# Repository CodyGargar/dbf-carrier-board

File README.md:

# MIT DBF Logger + Stabilizer board (Rev B)

Everything for the Teensy 4.1 board that stabilizes the plane, sends telemetry to the pilot's radio and logs every flight.
Status: **routed and order-ready (Rev B)**. Every connection is routed, the design check has no electrical errors, and the JLCPCB files are in [jlcpcb/](jlcpcb/). All pin orders are checked (see Open questions).

| File | What it is |
|---|---|
| [wiring/avionics-wiring.png](wiring/avionics-wiring.png) | **Full avionics wiring diagram**: both batteries, receiver, board, servos, ESC and motor (SVG next to it) |
| [design-spec.md](design-spec.md) | How the board works: failover, ESC telemetry, power, pins, bring-up order |
| [kicad/dbf-carrier.kicad_pro](kicad/dbf-carrier.kicad_pro) | KiCad project; open it in KiCad 7 or newer |
| [kicad/board-top.png](kicad/board-top.png) | Picture of the routed board (red = top copper, blue = bottom copper) |
| [kicad/board-inner-planes.png](kicad/board-inner-planes.png) | The two inner layers: ground plane and servo-power plane |
| [jlcpcb/ORDERING.md](jlcpcb/ORDERING.md) | How to order: Gerber zip, parts list (BOM) and placement file (CPL) for JLCPCB |
| [kicad/drc-report.txt](kicad/drc-report.txt) | Design check output: 0 shorts, 0 clearance errors, 0 unconnected pins |
| [pinout.csv](pinout.csv) | Which Teensy pin does what |
| [parts-list.xlsx](parts-list.xlsx) / [bom.csv](bom.csv) | Parts with links and prices; about $369 for one plane set + 2 built boards |
| [module-menu.md](module-menu.md) | Every module, and whether it is needed or optional |
| [rules-check-2027.md](rules-check-2027.md) | 2027 rules draft and last year's Q&A, checked against the board |

Online versions:
- Board slide deck: https://claude.ai/artifact/GLwo9eBtNZT7Tdii5Wy8GB

## Changes on 2026-11-07 (before ordering)

- **RX CRSF connector (J6) now matches the RadioMaster ER8's CRSF port** (⊖, +, RX, TX), so a standard pin-1-to-pin-1 JST-GH cable works. Pin 2 (the receiver's 5 V) is left unconnected on the board.
- **ESC is the Castle Phoenix Edge 100** (34 V, 100 A, 5 A BEC), not the Edge Lite. The **+ pin of the T column on TO SERVOS + ESC is now unconnected**, so the ESC's BEC can never feed the servo rail, even if its red wire is left in.
- Rerouted, design check rerun (0 unconnected pads, no new warnings), JLCPCB files regenerated. **Re-upload the Gerber zip, BOM and CPL to JLCPCB before paying, and set the part rotations again** (see [jlcpcb/ORDERING.md](jlcpcb/ORDERING.md)).

## Open questions

Nothing blocks the JLCPCB order now. Still open:

1. Confirm in this year's Q&A that a custom microcontroller stabilization system is allowed. Ask about the optional inline current sensor too (the ESC's own telemetry avoids it).
2. Bench-test Castle Link Live with the board's 10k pull-up to 3.3 V (Castle's adapters use 10k to the receiver's +). If it doesn't work, R9 can be changed by hand.
3. **Servo voltage:** the receiver pack is a 2S LiPo (8.4 V fully charged) and feeds the servos directly. **Every servo must be rated HV (8.4 V).** Also confirm the ER8 accepts 8.4 V on its servo pins. If any servo is 6 V only, switch to a 2S LiFe (7.2 V full) pack.
4. Confirm how the 2 drop servos are wired (Y-cable on receiver channel 8).

Done:
- **Batteries chosen (2026-11-07):** motor pack is a Turnigy nano-tech 6S LiPo, 22.2 V, 3300 mAh (73 Wh, under the 100 Wh limit; 25.2 V full, well under the ESC's 34 V). Receiver pack is a 2S LiPo, 7.4 V, 1300 mAh (9.6 Wh).
- **Pololu S7V7F5 pin order checked:** GND is the middle pin, with VIN and VOUT on the ends (two independent CAD libraries for this module agree; Pololu lists them as VIN, GND, VOUT). The board matches. The only way to get it wrong is to put the module in backwards, so the board now has **VIN / GND / OUT** printed under the pads: VIN goes in the square pad.
- **Buzzer + pad checked:** two footprints drawn from the CMT-8504 datasheet (one marks the pads P and N, one cites the datasheet's rev 09/11/2024 land pattern) both put **+ at the top-left pad and − at the bottom-left**, with the right pair as dummy pads. KiCad's pad 1 is the same top-left pad, and the board wires it to +. Correct as is.
- Receiver confirmed as a **RadioMaster ER8 2.4 GHz**. Its CRSF port order (⊖, +, RX, TX) was checked from a photo, and the board now matches it.

## ESC setup (Castle Phoenix Edge 100)

1. Pull the **red** wire out of the ESC's throttle plug (lift the tab with a needle) and shrink-wrap it. The board already ignores it, but this shows the BEC is disabled at tech inspection (rules 3.2.3).
2. With a Castle Link USB adapter, turn **Link Live on**, set **fixed throttle endpoints** (not auto-calibrate), and check the low-voltage cutoff matches your cell count.
3. Plug the throttle lead into **T** on TO SERVOS + ESC, with the signal wire on S.

## CRSF cable (ER8 to board)

Use a JST-GH 1.25 mm 4-pin cable wired **pin 1 to pin 1** (same direction), not a reversed one. Before plugging in the Teensy, power the receiver and check with a meter: 5 V should appear only on J6 pin 2.

## Regenerating the board

The board is generated by Python scripts that use KiCad's `pcbnew` module (KiCad 7). Run them in order from the `kicad/` folder:

```
python3 make_board.py     # places the parts
python3 route_board.py    # routes every connection
python3 finish_board.py   # planes, design check, JLCPCB files
```

The wiring diagram is drawn by `wiring/make_wiring.py`.

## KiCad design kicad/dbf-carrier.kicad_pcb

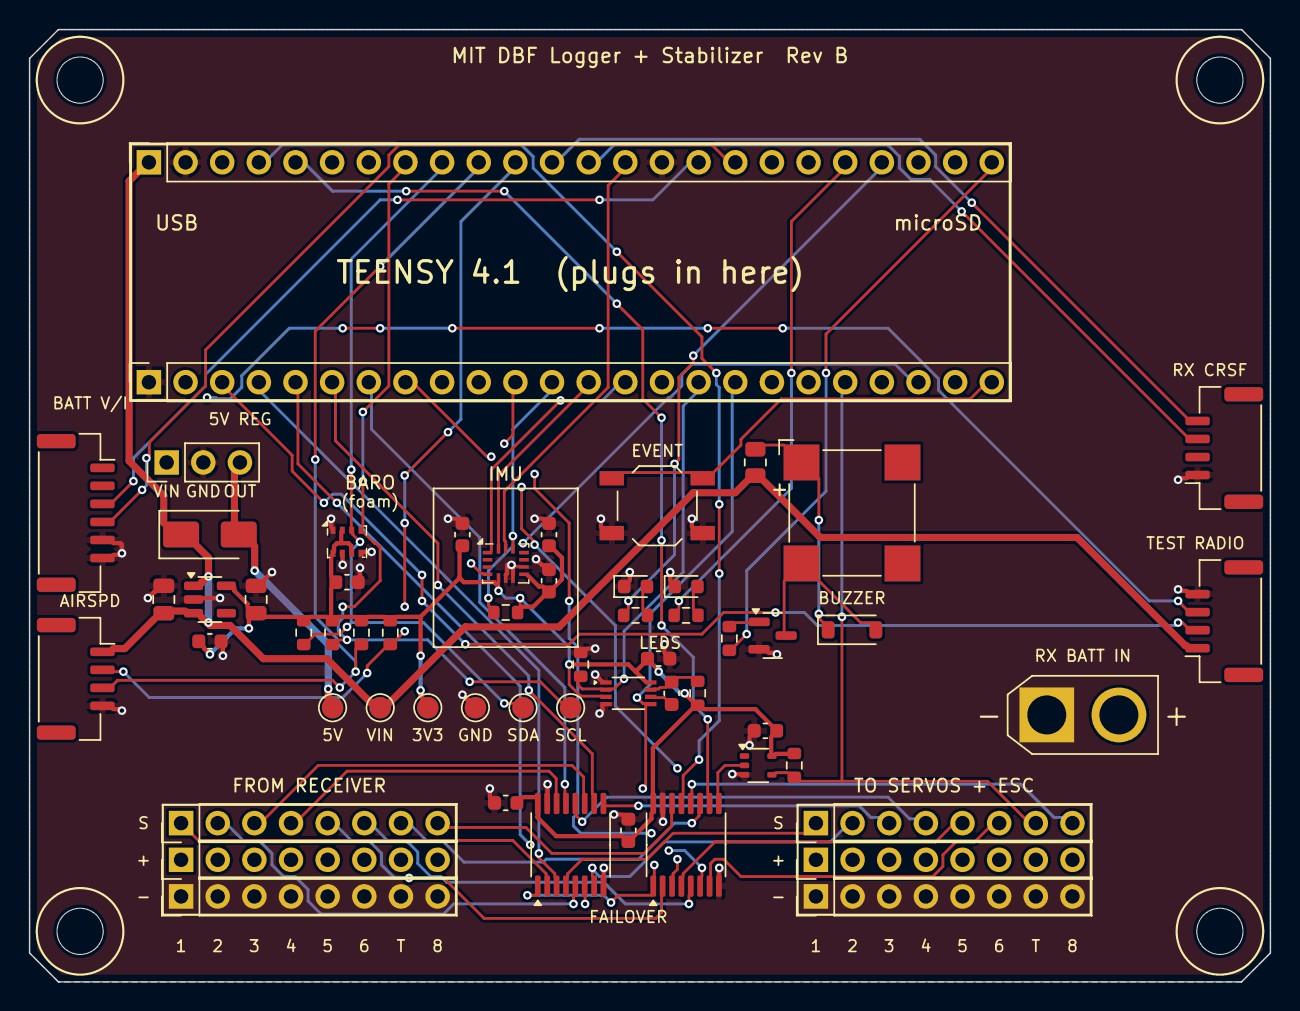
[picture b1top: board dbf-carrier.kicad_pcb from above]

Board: 4 copper layers, 86.0 x 66.0 mm, 62 parts (0 on the bottom side), 58 nets.

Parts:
BZ1: Buzzer; MagneticBuzzer_CUI_CMT-8504-100-SMT
C1, C2: 10uF; C_0805_2012Metric
C3, C4, C5, C6, C8, C9, C10, C11: 100nF; C_0603_1608Metric
C7: watchdog RC; C_0603_1608Metric
C12: 2.2uF; C_0603_1608Metric
D1: SS24 Schottky; D_SMA
D2: GRN; LED_0603_1608Metric
D3: RED; LED_0603_1608Metric
D4: 1N4148W flyback; D_SOD-123
H1, H2, H3, H4: M3; MountingHole_3.2mm_M3
J1: Teensy row A; PinSocket_1x24_P2.54mm_Vertical
J2: Teensy row B; PinSocket_1x24_P2.54mm_Vertical
J4: Airspeed; JST_GH_SM04B-GHS-TB_1x04-1MP_P1.25mm_Horizontal
J6: RX CRSF; JST_GH_SM04B-GHS-TB_1x04-1MP_P1.25mm_Horizontal
J7: Power module (sense only); JST_GH_SM06B-GHS-TB_1x06-1MP_P1.25mm_Horizontal
J11: Test radio (testing only); JST_GH_SM04B-GHS-TB_1x04-1MP_P1.25mm_Horizontal
J12: Rx battery in (from radio switch); AMASS_XT30U-M_1x02_P5.0mm_Vertical
J21: FROM RECEIVER S; PinHeader_1x08_P2.54mm_Vertical
J22: FROM RECEIVER +; PinHeader_1x08_P2.54mm_Vertical
J23: FROM RECEIVER -; PinHeader_1x08_P2.54mm_Vertical
J31: TO SERVOS + ESC S; PinHeader_1x08_P2.54mm_Vertical
J32: TO SERVOS + ESC +; PinHeader_1x08_P2.54mm_Vertical
J33: TO SERVOS + ESC -; PinHeader_1x08_P2.54mm_Vertical
Q1: MMBT3904 NPN; SOT-23
R1: 10k CS pull-up; R_0603_1608Metric
R2: 4.7k SDA; R_0603_1608Metric
R3: 4.7k SCL; R_0603_1608Metric
R4: 2.2k SDA1; R_0603_1608Metric
R5: 2.2k SCL1; R_0603_1608Metric
R6, R7: 1k; R_0603_1608Metric
R8: watchdog RC; R_0603_1608Metric
R9: 10k throttle pull-up; R_0603_1608Metric
R10: 1k buzzer base; R_0603_1608Metric
R11: 100k heartbeat pull-down; R_0603_1608Metric
R12: 18R buzzer current limit; R_0805_2012Metric
SW1: Event button; SW_SPST_TL3342
TP1: 5V; TestPoint_Pad_D1.5mm
TP2: VIN; TestPoint_Pad_D1.5mm
TP3: 3V3; TestPoint_Pad_D1.5mm
TP4: GND; TestPoint_Pad_D1.5mm
TP5: SDA; TestPoint_Pad_D1.5mm
TP6: SCL; TestPoint_Pad_D1.5mm
U2: ICM-42688-P; Bosch_LGA-14_3x2.5mm_P0.5mm
U3: DPS368; Bosch_LGA-8_2x2.5mm_P0.65mm_ClockwisePinNumbering
U4: AP2112K-3.3; SOT-23-5
U5: Pololu S7V7F5 5V reg; PinHeader_1x03_P2.54mm_Vertical
U6: SN74LVC157A ch1-4; TSSOP-16_4.4x5mm_P0.65mm
U7: SN74LVC157A ch5-8; TSSOP-16_4.4x5mm_P0.65mm
U8: 74LVC1G123 watchdog; VSSOP-8_2.3x2mm_P0.5mm
U9: 74LVC1G07 throttle open-drain; SOT-353_SC-70-5

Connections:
+3V3S: C2.1, C3.1, C4.1, C5.1, C6.1, C8.2, C9.1, C10.1, C11.2, C12.1, R1.2, R2.2, R3.2, R4.2, R5.2, R8.2, R9.2, TP3.1, U2.5, U2.8, U3.2, U3.6, U3.8, U4.5, U6.16, U7.16, U8.3, U8.8, U9.5
+5V: D1.2, TP1.1, U5.3
BATT_I: J1.16, J7.3
BATT_V: J1.17, J7.4
BTN: J2.24, SW1.1
BUZ: J1.24, R10.1
BUZ_B: Q1.1, R10.2
BUZ_C: BZ1.2, D4.2, Q1.3
BUZ_P: BZ1.1, D4.1, R12.2
CRSF_RX: J1.12, J6.4
CRSF_TX: J1.13, J6.3
GND: C1.2, C2.2, C3.2, C4.2, C5.2, C6.2, C8.1, C9.2, C10.2, C11.1, C12.2, D2.1, D3.1, J1.2, J1.15, J2.1, J4.4, J6.1, J7.5, J7.6, J11.4, J12.1, J23.1, J23.2, J23.3, J23.4, J23.5, J23.6, J23.7, J23.8, J33.1, J33.2, J33.3, J33.4, J33.5, J33.6, J33.7, J33.8, Q1.2, R11.2, SW1.2, TP4.1, U2.6, U2.7, U2.9, U3.1, U3.5, U3.7, U4.2, U5.2, U6.8, U6.15, U7.8, U7.15, U8.1, U8.4, U9.3
HEARTBEAT: J2.16, R11.1, U8.2
IMU_CS: J2.12, R1.1, U2.12
IMU_INT: J2.22, U2.4
IMU_MISO: J2.14, U2.1
IMU_MOSI: J2.13, U2.14
IMU_SCK: J1.14, U2.13
LED_G: J1.21, R6.1
LED_G_A: D2.2, R6.2
LED_R: J1.20, R7.1
LED_R_A: D3.2, R7.2
OUT_CH1: J31.1, U6.4
OUT_CH2: J31.2, U6.7
OUT_CH3: J31.3, U6.9
OUT_CH4: J31.4, U6.12
OUT_CH5: J31.5, U7.4
OUT_CH6: J31.6, U7.7
OUT_CH8: J31.8, U7.12
OUT_T: J2.20, J31.7, R9.1, U9.4
PWM_CH1: J2.4, U6.3
PWM_CH2: J2.5, U6.6
PWM_CH3: J2.6, U6.10
PWM_CH4: J2.7, U6.13
PWM_CH5: J2.8, U7.3
PWM_CH6: J2.11, U7.6
PWM_CH8: J1.4, U7.13
PWM_CHT: J1.5, U7.10
RX_CH1: J21.1, U6.2
RX_CH2: J21.2, U6.5
RX_CH3: J21.3, U6.11
RX_CH4: J21.4, U6.14
RX_CH5: J21.5, U7.2
RX_CH6: J21.6, U7.5
RX_CH8: J21.8, U7.14
RX_CHT: J21.7, U7.11
SCL: J1.8, R3.1, TP6.1, U3.4
SCL1: J1.11, J4.2, R5.1
SDA: J1.9, R2.1, TP5.1, U3.3
SDA1: J1.10, J4.3, R4.1
TEENSY_OK: J2.17, U6.1, U7.1, U8.5
TEL_RX: J2.2, J11.3
TEL_TX: J2.3, J11.2
THR_MUX: U7.9, U9.2
VIN: C1.1, D1.1, J1.1, J4.1, J11.1, R12.1, TP2.1, U4.1, U4.3
VSERVO: J12.2, J22.1, J22.2, J22.3, J22.4, J22.5, J22.6, J22.7, J22.8, J32.1, J32.2, J32.3, J32.4, J32.5, J32.6, J32.8, U5.1
WD_C: C7.1, U8.6
WD_RC: C7.2, R8.1, U8.7

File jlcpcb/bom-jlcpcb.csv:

Comment,Designator,Footprint,LCSC Part #
CMT-8504-100-SMT-TR,BZ1,MagneticBuzzer_CUI_CMT-8504-100-SMT,
10uF 25V X5R 0805,"C1,C2",C_0805_2012Metric,
100nF X7R 0603,"C3,C4,C6,C8,C9,C10,C11",C_0603_1608Metric,
10nF X7R 0603,C5,C_0603_1608Metric,
0.47uF X7R 0603 (watchdog timing),C7,C_0603_1608Metric,
2.2uF X7R 0603,C12,C_0603_1608Metric,
SS24 (SMA),D1,D_SMA,
Green LED 0603,D2,LED_0603_1608Metric,
Red LED 0603,D3,LED_0603_1608Metric,
1N4148W (SOD-123),D4,D_SOD-123,
SM04B-GHS-TB(LF)(SN),"J4,J6,J11",JST_GH_SM04B-GHS-TB_1x04-1MP_P1.25mm_Horizontal,
SM06B-GHS-TB(LF)(SN),J7,JST_GH_SM06B-GHS-TB_1x06-1MP_P1.25mm_Horizontal,
MMBT3904,Q1,SOT-23,
10k,"R1,R9",R_0603_1608Metric,
4.7k,"R2,R3",R_0603_1608Metric,
2.2k,"R4,R5",R_0603_1608Metric,
1k,"R6,R7,R10",R_0603_1608Metric,
100k 1% (watchdog timing),R8,R_0603_1608Metric,
100k,R11,R_0603_1608Metric,
18R 0805,R12,R_0805_2012Metric,
TL3342F160QG,SW1,SW_SPST_TL3342,
ICM-42688-P,U2,Bosch_LGA-14_3x2.5mm_P0.5mm,
DPS368XTSA1,U3,Bosch_LGA-8_2x2.5mm_P0.65mm_ClockwisePinNumbering,
AP2112K-3.3TRG1,U4,SOT-23-5,
SN74LVC157APWR,"U6,U7",TSSOP-16_4.4x5mm_P0.65mm,
SN74LVC1G123DCUR,U8,VSSOP-8_2.3x2mm_P0.5mm,
SN74LVC1G07DCKR,U9,SOT-353_SC-70-5,
